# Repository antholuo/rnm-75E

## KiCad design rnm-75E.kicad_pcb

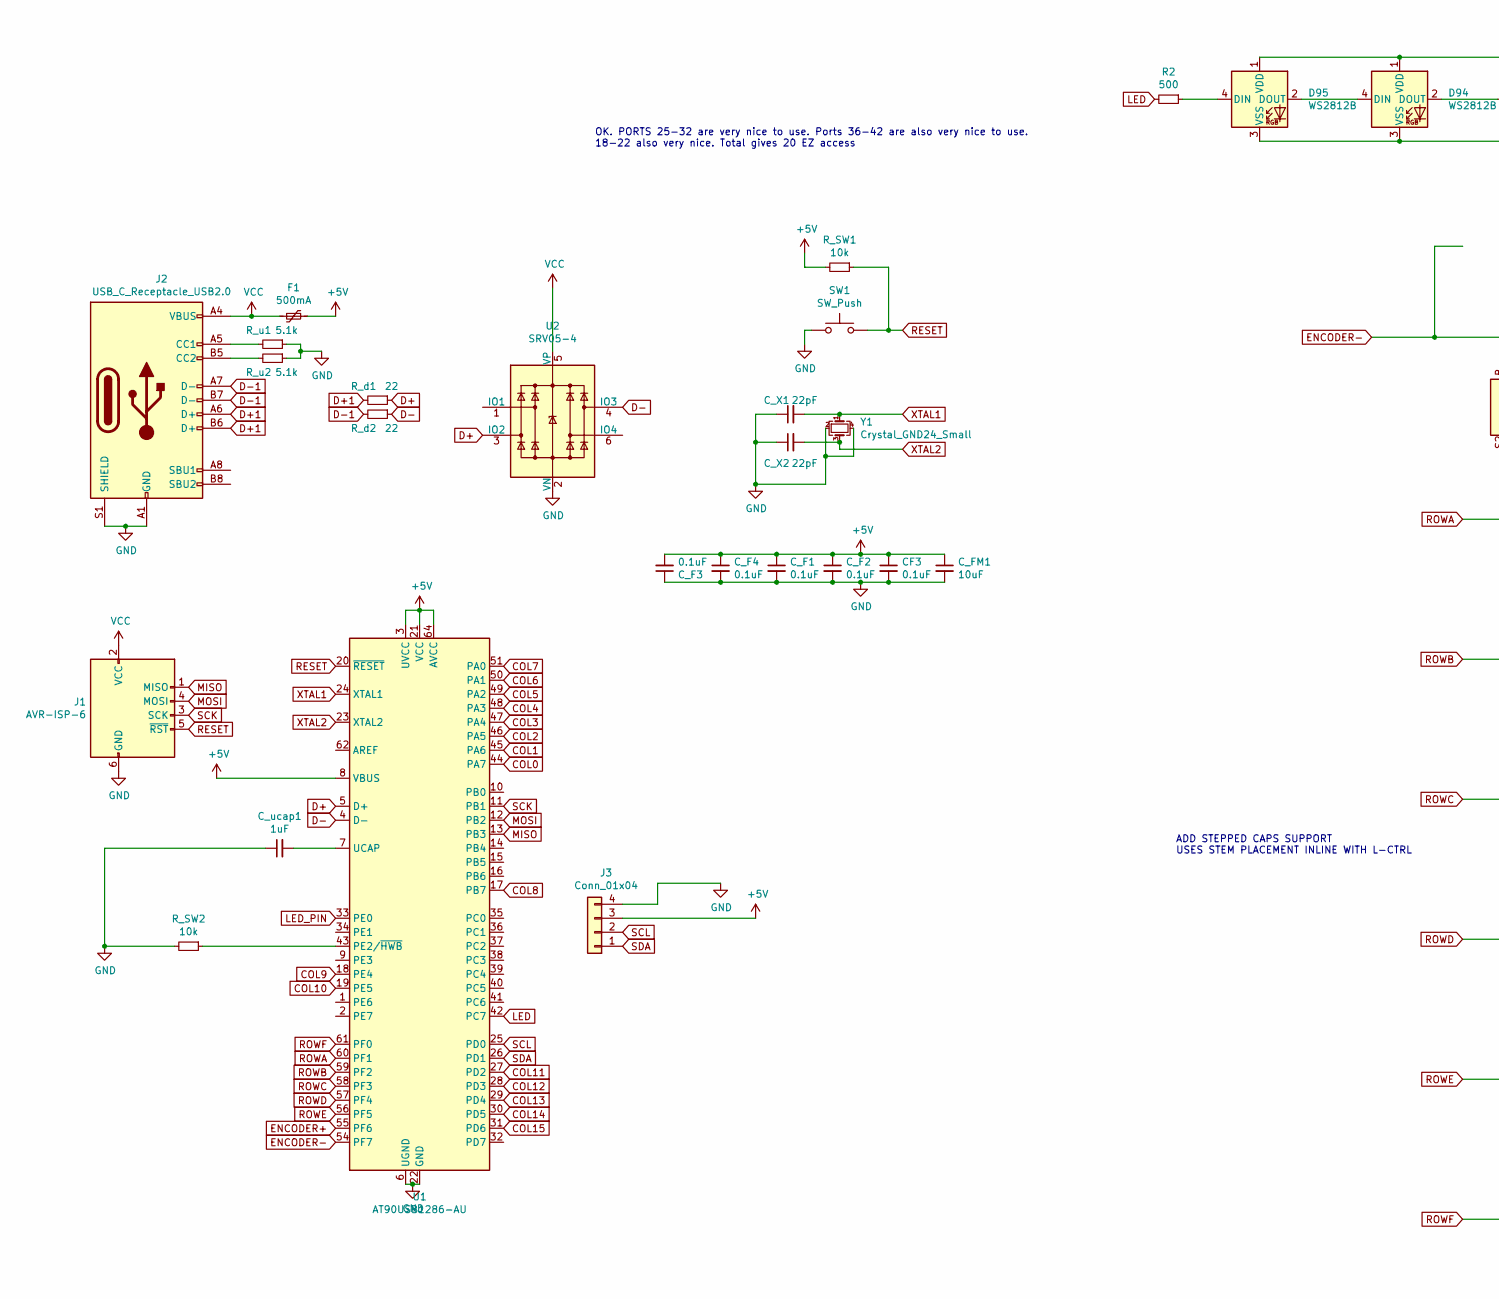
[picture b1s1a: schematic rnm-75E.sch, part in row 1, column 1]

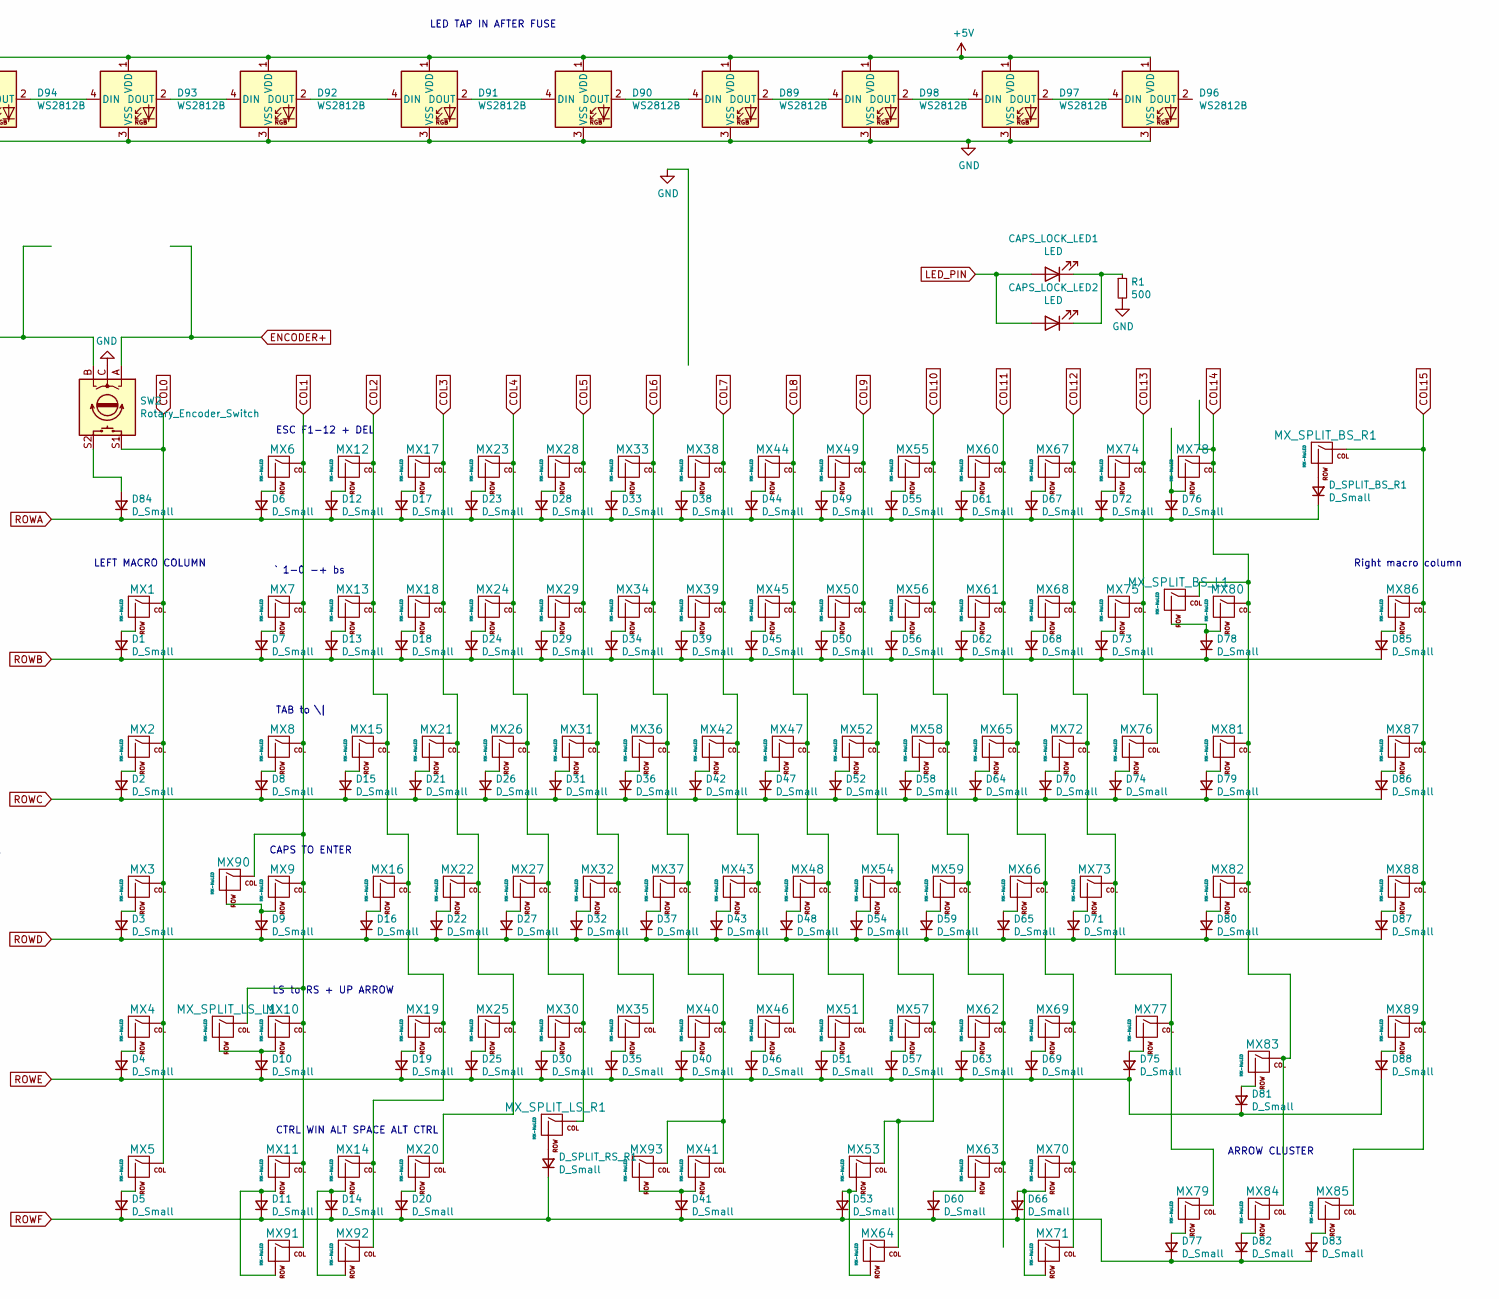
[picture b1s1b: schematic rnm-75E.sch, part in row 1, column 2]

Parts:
CAPS_LOCK_LED1, CAPS_LOCK_LED2: LED; LED_D3.0mm
CF3: 0.1uF; C_0805_2012Metric
C_F1, C_F2, C_F3, C_F4: 0.1uF; C_0805_2012Metric
C_FM1: 10uF; C_0805_2012Metric
C_X1, C_X2: 22pF; C_0805_2012Metric
C_ucap1: 1uF; C_0805_2012Metric
D1, D2, D3, D4, D5, D6, D7, D8, D9, D10, D11, D12, D13, D14, D15, D16, D17, D18, D19, D20, D21, D22, D23, D24, D25, D26, D27, D28, D29, D30, D31, D32, D33, D34, D35, D36, D37, D38, D39, D40, D41, D42, D43, D44, D45, D46, D47, D48, D49, D50, D51, D52, D53, D54, D55, D56, D57, D58, D59, D60, D61, D62, D63, D64, D65, D66, D67, D68, D69, D70, D71, D72, D73, D74, D75, D76, D77, D78, D79, D80, D81, D82, D83, D84, D85, D86, D87, D88: D_Small; D_SOD-123
D89, D90, D91, D92, D93, D94, D95, D96, D97, D98: WS2812B; LED_WS2812B_PLCC4_5.0x5.0mm_P3.2mm
D_SPLIT_BS_R1: D_Small; D_SOD-123
D_SPLIT_RS_R1: D_Small; D_SOD-123
F1: 500mA; Fuse_1206_3216Metric
J1: AVR-ISP-6; Reset_Pretty-Mask
J2: USB_C_Receptacle_USB2.0; USB_C_Receptacle_HRO_TYPE-C-31-M-12
J3: Conn_01x04; PinSocket_1x04_P2.54mm_Vertical
MX1, MX2, MX3, MX4, MX5, MX6, MX7, MX12, MX13, MX15, MX16, MX17, MX18, MX19, MX21, MX22, MX23, MX24, MX25, MX26, MX27, MX28, MX29, MX30, MX31, MX32, MX33, MX34, MX35, MX36, MX37, MX38, MX39, MX40, MX42, MX43, MX44, MX45, MX46, MX47, MX48, MX49, MX50, MX51, MX52, MX53, MX54, MX55, MX56, MX57, MX58, MX59, MX60, MX61, MX62, MX63, MX65, MX66, MX67, MX68, MX69, MX70, MX72, MX73, MX74, MX75, MX76, MX78, MX79, MX83, MX84, MX85, MX86, MX87, MX88, MX89: MX-NoLED; MXOnly-1U-NoLED
MX8, MX64, MX71, MX81, MX91, MX92: MX-NoLED; MXOnly-1.5U-NoLED
MX9, MX77: MX-NoLED; MXOnly-1.75U-NoLED
MX10, MX82: MX-NoLED; MXOnly-2.25U-NoLED
MX11, MX14, MX20, MX90: MX-NoLED; MXOnly-1.25U-NoLED
MX41: MX-NoLED; MXOnly-6.25U-ReversedStabilizers-NoLED
MX80: MX-NoLED; MXOnly-2U-NoLED
MX93: MX-NoLED; MXOnly-7U-ReversedStabilizers-NoLED
MX_SPLIT_BS_L1: MX-NoLED; MXOnly-1U-NoLED
MX_SPLIT_BS_R1: MX-NoLED; MXOnly-1U-NoLED
MX_SPLIT_LS_L1: MX-NoLED; MXOnly-1.25U-NoLED
MX_SPLIT_LS_R1: MX-NoLED; MXOnly-1U-NoLED
R1, R2: 500; R_0805_2012Metric
R_SW1, R_SW2: 10k; R_0805_2012Metric
R_d1, R_d2: 22; R_0805_2012Metric
R_u1, R_u2: 5.1k; R_0805_2012Metric
SW1: SW_Push; SKQG-1155865
SW2: Rotary_Encoder_Switch; RotaryEncoder_Alps_EC11E-Switch_Vertical_H20mm
U1: AT90USB1286-AU; TQFP-64_14x14mm_P0.8mm
U2: SRV05-4; SOT-23-6
Y1: Crystal_GND24_Small; Crystal_SMD_3225-4Pin_3.2x2.5mm

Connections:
+5V: CF3.1, C_F1.1, C_F2.1, C_F3.2, C_F4.1, C_FM1.1, D89.1 (VDD), D90.1 (VDD), D91.1 (VDD), D92.1 (VDD), D93.1 (VDD), D94.1 (VDD), D95.1 (VDD), D96.1 (VDD), D97.1 (VDD), D98.1 (VDD), F1.1, J3.3, R_SW1.2, U1.3 (UVCC), U1.8 (VBUS), U1.21 (VCC), U1.52 (VCC), U1.64 (AVCC)
COL0: MX1.1 (COL), MX2.1 (COL), MX3.1 (COL), MX4.1 (COL), MX5.1 (COL), SW2.S1, U1.44 (PA7)
COL1: MX6.1 (COL), MX7.1 (COL), MX8.1 (COL), MX9.1 (COL), MX10.1 (COL), MX11.1 (COL), MX90.1 (COL), MX91.1 (COL), MX_SPLIT_LS_L1.1 (COL), U1.45 (PA6)
COL2: MX12.1 (COL), MX13.1 (COL), MX14.1 (COL), MX15.1 (COL), MX16.1 (COL), MX19.1 (COL), MX92.1 (COL), U1.46 (PA5)
COL3: MX17.1 (COL), MX18.1 (COL), MX20.1 (COL), MX21.1 (COL), MX22.1 (COL), MX25.1 (COL), U1.47 (PA4)
COL4: MX23.1 (COL), MX24.1 (COL), MX26.1 (COL), MX27.1 (COL), MX30.1 (COL), MX_SPLIT_LS_R1.1 (COL), U1.48 (PA3)
COL5: MX28.1 (COL), MX29.1 (COL), MX31.1 (COL), MX32.1 (COL), MX35.1 (COL), U1.49 (PA2)
COL6: MX33.1 (COL), MX34.1 (COL), MX36.1 (COL), MX37.1 (COL), MX40.1 (COL), MX41.1 (COL), MX93.1 (COL), U1.50 (PA1)
COL7: MX38.1 (COL), MX39.1 (COL), MX42.1 (COL), MX43.1 (COL), MX46.1 (COL), U1.51 (PA0)
COL8: MX44.1 (COL), MX45.1 (COL), MX47.1 (COL), MX48.1 (COL), MX51.1 (COL), U1.17 (PB7)
COL9: MX49.1 (COL), MX50.1 (COL), MX52.1 (COL), MX53.1 (COL), MX54.1 (COL), MX57.1 (COL), MX64.1 (COL), U1.18 (PE4)
COL10: MX55.1 (COL), MX56.1 (COL), MX58.1 (COL), MX59.1 (COL), MX62.1 (COL), MX63.1 (COL), U1.19 (PE5)
COL11: MX60.1 (COL), MX61.1 (COL), MX65.1 (COL), MX66.1 (COL), MX69.1 (COL), MX70.1 (COL), MX71.1 (COL), U1.27 (PD2)
COL12: MX67.1 (COL), MX68.1 (COL), MX72.1 (COL), MX73.1 (COL), MX77.1 (COL), MX79.1 (COL), U1.28 (PD3)
COL13: MX74.1 (COL), MX75.1 (COL), MX76.1 (COL), U1.29 (PD4)
COL14: MX78.1 (COL), MX80.1 (COL), MX81.1 (COL), MX82.1 (COL), MX83.1 (COL), MX84.1 (COL), MX_SPLIT_BS_L1.1 (COL), U1.30 (PD5)
COL15: MX85.1 (COL), MX86.1 (COL), MX87.1 (COL), MX88.1 (COL), MX89.1 (COL), MX_SPLIT_BS_R1.1 (COL), U1.31 (PD6)
D+: R_d1.1, U1.5 (D+), U2.3 (IO2)
D+1: J2.A6 (D+), J2.B6 (D+), R_d1.2
D-: R_d2.1, U1.4 (D-), U2.4 (IO3)
D-1: J2.A7 (D-), J2.B7 (D-), R_d2.2
ENCODER+: SW2.A, U1.55 (PF6)
ENCODER-: SW2.B, U1.54 (PF7)
GND: CF3.2, C_F1.2, C_F2.2, C_F3.1, C_F4.2, C_FM1.2, C_X1.1, C_X2.1, C_ucap1.1, D89.3 (VSS), D90.3 (VSS), D91.3 (VSS), D92.3 (VSS), D93.3 (VSS), D94.3 (VSS), D95.3 (VSS), D96.3 (VSS), D97.3 (VSS), D98.3 (VSS), J1.6 (GND), J2.A1 (GND), J2.A12 (GND), J2.B1 (GND), J2.B12 (GND), J2.S1 (SHIELD), J3.4, R1.2, R_SW2.2, R_u1.1, R_u2.1, SW1.1, SW2.C, U1.6 (UGND), U1.22 (GND), U1.53 (GND), U1.63 (GND), U2.2 (VN), Y1.2, Y1.4
LED: R2.2, U1.42 (PC7)
LED_PIN: CAPS_LOCK_LED1.2 (A), CAPS_LOCK_LED2.2 (A), U1.33 (PE0)
MISO: J1.1 (MISO), U1.13 (PB3)
MOSI: J1.4 (MOSI), U1.12 (PB2)
unnamed: CAPS_LOCK_LED1.1 (K), CAPS_LOCK_LED2.1 (K), R1.1
unnamed: C_ucap1.2, U1.7 (UCAP)
unnamed: D1.2 (A), MX1.2 (ROW)
unnamed: D2.2 (A), MX2.2 (ROW)
unnamed: D3.2 (A), MX3.2 (ROW)
unnamed: D4.2 (A), MX4.2 (ROW)
unnamed: D5.2 (A), MX5.2 (ROW)
unnamed: D6.2 (A), MX6.2 (ROW)
unnamed: D7.2 (A), MX7.2 (ROW)
unnamed: D8.2 (A), MX8.2 (ROW)
unnamed: D9.2 (A), MX9.2 (ROW), MX90.2 (ROW)
unnamed: D10.2 (A), MX10.2 (ROW), MX_SPLIT_LS_L1.2 (ROW)
unnamed: D11.2 (A), MX11.2 (ROW), MX91.2 (ROW)
unnamed: D12.2 (A), MX12.2 (ROW)
unnamed: D13.2 (A), MX13.2 (ROW)
unnamed: D14.2 (A), MX14.2 (ROW), MX92.2 (ROW)
unnamed: D15.2 (A), MX15.2 (ROW)
unnamed: D16.2 (A), MX16.2 (ROW)
unnamed: D17.2 (A), MX17.2 (ROW)
unnamed: D18.2 (A), MX18.2 (ROW)
unnamed: D19.2 (A), MX19.2 (ROW)
unnamed: D20.2 (A), MX20.2 (ROW)
unnamed: D21.2 (A), MX21.2 (ROW)
unnamed: D22.2 (A), MX22.2 (ROW)
unnamed: D23.2 (A), MX23.2 (ROW)
unnamed: D24.2 (A), MX24.2 (ROW)
unnamed: D25.2 (A), MX25.2 (ROW)
unnamed: D26.2 (A), MX26.2 (ROW)
unnamed: D27.2 (A), MX27.2 (ROW)
unnamed: D28.2 (A), MX28.2 (ROW)
unnamed: D29.2 (A), MX29.2 (ROW)
unnamed: D30.2 (A), MX30.2 (ROW)
unnamed: D31.2 (A), MX31.2 (ROW)
unnamed: D32.2 (A), MX32.2 (ROW)
unnamed: D33.2 (A), MX33.2 (ROW)
unnamed: D34.2 (A), MX34.2 (ROW)
unnamed: D35.2 (A), MX35.2 (ROW)
unnamed: D36.2 (A), MX36.2 (ROW)
unnamed: D37.2 (A), MX37.2 (ROW)
unnamed: D38.2 (A), MX38.2 (ROW)
unnamed: D39.2 (A), MX39.2 (ROW)
unnamed: D40.2 (A), MX40.2 (ROW)
unnamed: D41.2 (A), MX41.2 (ROW), MX93.2 (ROW)
unnamed: D42.2 (A), MX42.2 (ROW)
unnamed: D43.2 (A), MX43.2 (ROW)
unnamed: D44.2 (A), MX44.2 (ROW)
unnamed: D45.2 (A), MX45.2 (ROW)
unnamed: D46.2 (A), MX46.2 (ROW)
unnamed: D47.2 (A), MX47.2 (ROW)
unnamed: D48.2 (A), MX48.2 (ROW)
unnamed: D49.2 (A), MX49.2 (ROW)
unnamed: D50.2 (A), MX50.2 (ROW)
unnamed: D51.2 (A), MX51.2 (ROW)
unnamed: D52.2 (A), MX52.2 (ROW)
unnamed: D53.2 (A), MX53.2 (ROW), MX64.2 (ROW)
unnamed: D54.2 (A), MX54.2 (ROW)
unnamed: D55.2 (A), MX55.2 (ROW)
unnamed: D56.2 (A), MX56.2 (ROW)
unnamed: D57.2 (A), MX57.2 (ROW)
unnamed: D58.2 (A), MX58.2 (ROW)
unnamed: D59.2 (A), MX59.2 (ROW)
unnamed: D60.2 (A), MX63.2 (ROW)
unnamed: D61.2 (A), MX60.2 (ROW)
unnamed: D62.2 (A), MX61.2 (ROW)
unnamed: D63.2 (A), MX62.2 (ROW)
unnamed: D64.2 (A), MX65.2 (ROW)
unnamed: D65.2 (A), MX66.2 (ROW)
unnamed: D66.2 (A), MX70.2 (ROW), MX71.2 (ROW)
unnamed: D67.2 (A), MX67.2 (ROW)
unnamed: D68.2 (A), MX68.2 (ROW)
unnamed: D69.2 (A), MX69.2 (ROW)
unnamed: D70.2 (A), MX72.2 (ROW)
unnamed: D71.2 (A), MX73.2 (ROW)
unnamed: D72.2 (A), MX74.2 (ROW)
unnamed: D73.2 (A), MX75.2 (ROW)
unnamed: D74.2 (A), MX76.2 (ROW)
unnamed: D75.2 (A), MX77.2 (ROW)
unnamed: D76.2 (A), MX78.2 (ROW)
unnamed: D77.2 (A), MX79.2 (ROW)
unnamed: D78.2 (A), MX80.2 (ROW), MX_SPLIT_BS_L1.2 (ROW)
unnamed: D79.2 (A), MX81.2 (ROW)
unnamed: D80.2 (A), MX82.2 (ROW)
unnamed: D81.2 (A), MX83.2 (ROW)
unnamed: D82.2 (A), MX84.2 (ROW)
unnamed: D83.2 (A), MX85.2 (ROW)
unnamed: D84.2 (A), SW2.S2
unnamed: D85.2 (A), MX86.2 (ROW)
unnamed: D86.2 (A), MX87.2 (ROW)
unnamed: D87.2 (A), MX88.2 (ROW)
unnamed: D88.2 (A), MX89.2 (ROW)
unnamed: D89.2 (DOUT), D98.4 (DIN)
unnamed: D89.4 (DIN), D90.2 (DOUT)
unnamed: D90.4 (DIN), D91.2 (DOUT)
unnamed: D91.4 (DIN), D92.2 (DOUT)
unnamed: D92.4 (DIN), D93.2 (DOUT)
unnamed: D93.4 (DIN), D94.2 (DOUT)
unnamed: D94.4 (DIN), D95.2 (DOUT)
unnamed: D95.4 (DIN), R2.1
unnamed: D96.4 (DIN), D97.2 (DOUT)
unnamed: D97.4 (DIN), D98.2 (DOUT)
unnamed: D_SPLIT_BS_R1.2 (A), MX_SPLIT_BS_R1.2 (ROW)
unnamed: D_SPLIT_RS_R1.2 (A), MX_SPLIT_LS_R1.2 (ROW)
unnamed: J2.A5 (CC1), R_u1.2
unnamed: J2.B5 (CC2), R_u2.2
unnamed: R_SW2.1, U1.43 (PE2/~HWB)
RESET: J1.5 (~RST), R_SW1.1, SW1.2, U1.20 (~RESET)
ROWA: D6.1 (K), D12.1 (K), D17.1 (K), D23.1 (K), D28.1 (K), D33.1 (K), D38.1 (K), D44.1 (K), D49.1 (K), D55.1 (K), D61.1 (K), D67.1 (K), D72.1 (K), D76.1 (K), D84.1 (K), D_SPLIT_BS_R1.1 (K), U1.60 (PF1)
ROWB: D1.1 (K), D7.1 (K), D13.1 (K), D18.1 (K), D24.1 (K), D29.1 (K), D34.1 (K), D39.1 (K), D45.1 (K), D50.1 (K), D56.1 (K), D62.1 (K), D68.1 (K), D73.1 (K), D78.1 (K), D85.1 (K), U1.59 (PF2)
ROWC: D2.1 (K), D8.1 (K), D15.1 (K), D21.1 (K), D26.1 (K), D31.1 (K), D36.1 (K), D42.1 (K), D47.1 (K), D52.1 (K), D58.1 (K), D64.1 (K), D70.1 (K), D74.1 (K), D79.1 (K), D86.1 (K), U1.58 (PF3)
ROWD: D3.1 (K), D9.1 (K), D16.1 (K), D22.1 (K), D27.1 (K), D32.1 (K), D37.1 (K), D43.1 (K), D48.1 (K), D54.1 (K), D59.1 (K), D65.1 (K), D71.1 (K), D80.1 (K), D87.1 (K), U1.57 (PF4)
ROWE: D4.1 (K), D10.1 (K), D19.1 (K), D25.1 (K), D30.1 (K), D35.1 (K), D40.1 (K), D46.1 (K), D51.1 (K), D57.1 (K), D63.1 (K), D69.1 (K), D75.1 (K), D81.1 (K), D88.1 (K), U1.56 (PF5)
ROWF: D5.1 (K), D11.1 (K), D14.1 (K), D20.1 (K), D41.1 (K), D53.1 (K), D60.1 (K), D66.1 (K), D77.1 (K), D82.1 (K), D83.1 (K), D_SPLIT_RS_R1.1 (K), U1.61 (PF0)
SCK: J1.3 (SCK), U1.11 (PB1)
SCL: J3.2, U1.25 (PD0)
SDA: J3.1, U1.26 (PD1)
VCC: F1.2, J1.2 (VCC), J2.A4 (VBUS), J2.A9 (VBUS), J2.B4 (VBUS), J2.B9 (VBUS), U2.5 (VP)
XTAL1: C_X1.2, U1.24 (XTAL1), Y1.1
XTAL2: C_X2.2, U1.23 (XTAL2), Y1.3

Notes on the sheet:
OK. PORTS 25-32 are very nice to use. Ports 36-42 are also very nice to use. 18-22 also very nice. Total gives 20 EZ access
ESC F1-12 + DEL
` 1-0 -+ bs
TAB to \|
CAPS TO ENTER
LS to RS + UP ARROW
Right macro column
ARROW CLUSTER
CTRL WIN ALT SPACE ALT CTRL
LEFT MACRO COLUMN
LED TAP IN AFTER FUSE
ADD STEPPED CAPS SUPPORT USES STEM PLACEMENT INLINE WITH L-CTRL

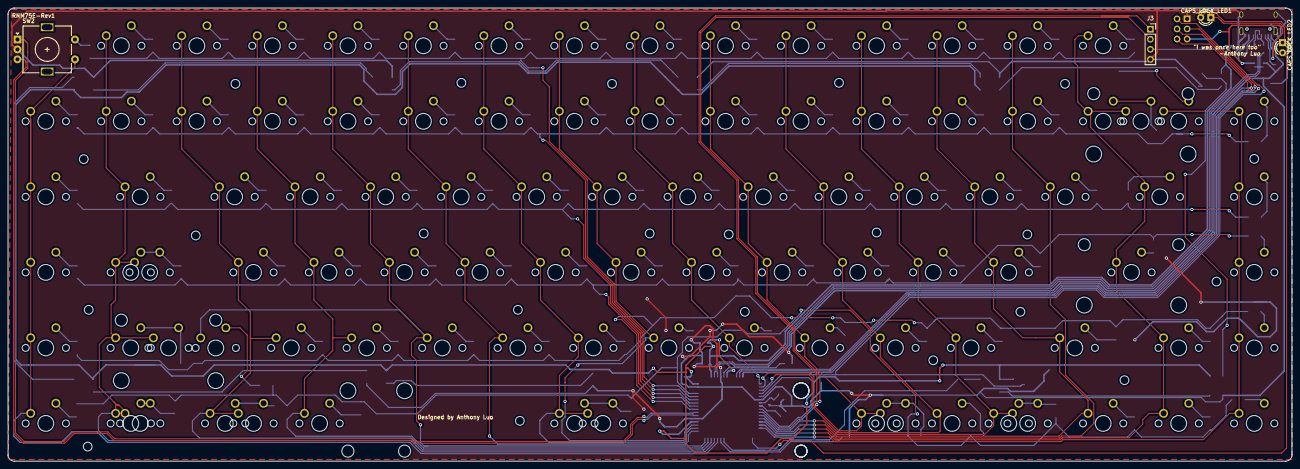
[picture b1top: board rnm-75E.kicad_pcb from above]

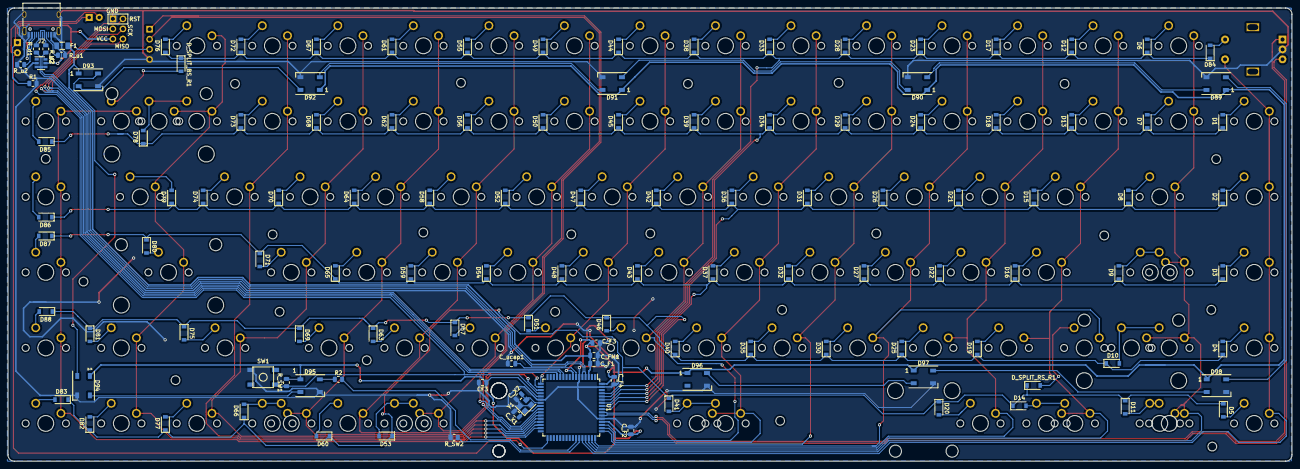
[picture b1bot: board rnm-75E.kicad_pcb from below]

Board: 2 copper layers, 323.9 x 114.3 mm, 225 parts (124 on the bottom side), 146 nets.

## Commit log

2021-05-10 init proj
2021-05-10 add submodules
2021-05-10 added libs
2021-05-10 mcu side
2021-05-11 new crystal
2021-05-11 mcu complete?
2021-05-11 ref made
2021-05-12 ROUTED
2021-05-12 added ground fill
2021-05-12 keyboard schematic done
2021-05-12 autosave
2021-05-12 wrong encoder
2021-05-12 place encoder
2021-05-12 update mcu
2021-05-12 pcb arranged
    diodes added
2021-05-12 exports
2021-05-13 Added TODO
2021-05-13 stepped caps_lock
2021-05-13 update todo
2021-05-13 added 7u space support
2021-05-13 double caps lock led
2021-05-13 wiring for row 1->4
2021-05-13 route scl/sda
2021-05-13 WIRED SPI
2021-05-13 move sw res
2021-05-13 route column 1-6
2021-05-13 route c7/8
2021-05-13 row 7 connected
2021-05-13 route row A-E onto mcu
2021-05-13 routed encoder
2021-05-13 Route rows 11/-15
2021-05-13 visual changes
2021-05-13 neater route 13
2021-05-13 oled and top gnd
2021-05-13 emcoder routing
2021-05-13 update LED net
2021-05-13 pretty
2021-05-13 add ISP
2021-05-13 all mcu connected
2021-05-13 update ground fill
2021-05-13 update fill zones
2021-05-13 routed to clear crystal
2021-05-13 renders
2021-05-13 gerbers
2021-05-13 update led resistor
2021-05-13 usb vcc routing
2021-05-13 bom + new gerber
2021-05-13 mounting locations
2021-05-13 update vias
2021-05-13 routing changes
2021-05-13 More stable design
2021-05-13 TODO
2021-05-13 added new mcu
2021-05-13 replacement added
2021-05-13 wiring touch ups
2021-05-13 srv05 added
2021-05-13 update fill
2021-05-13 drc changes
2021-05-14 updated crystal position
2021-05-14 ground fill
2021-05-14 no mounting holes
2021-05-14 updated D+/D-
2021-05-14 rerun main ground
2021-05-14 updated esd gnd
2021-05-14 update b.cu fill
2021-05-14 swap to hro usbc
2021-05-14 autosave hro
2021-05-14 length tuning
2021-05-14 hro usb
2021-05-14 crystal arrangement
2021-05-14 crystal gnd routing changes
2021-05-14 updated led 5v to 15mil rail
2021-05-14 ground mcu 53
2021-05-14 re-routed
2021-05-14 moved right side diodes
2021-05-14 silkscreen
2021-05-14 update rs_sw power rail
2021-05-14 reroute differential pair
2021-05-14 update rotary encoder
2021-05-14 update encoder
2021-05-14 split ls/bs
2021-05-14 wiring
2021-05-14 outputs
2021-05-15 plates
2021-05-15 update ground caps
2021-05-15 reroute main ground
2021-05-15 plate generation
2021-05-16 models
2021-05-16 oleds
2021-05-16 fancy plate and new oleds
2021-05-16 no iso enter
2021-05-16 new 3d models
2021-05-16 ignore
2021-05-17 sent to manu
2021-05-18 with holes step
2021-05-18 plateee
2021-05-18 plate
2021-05-18 gerber3
2021-05-18 plate3 gerbers
2021-05-18 screaming
2021-05-18 small holes
2021-05-18 new plate
2021-05-22 midlayers
2021-05-29 plate layout
2021-05-29 firmware1
2021-05-29 basic firmware
2021-06-19 pages
